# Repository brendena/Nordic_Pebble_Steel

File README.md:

# Nordic steel

The goal of this project is to replace the main motherboard in the pebble steel with newer parts.  Specifically the cpu will be a Nordic NRF52840.

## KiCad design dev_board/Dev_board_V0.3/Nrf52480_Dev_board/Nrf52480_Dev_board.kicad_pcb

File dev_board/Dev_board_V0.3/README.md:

# Changes
* Add i2c pull up resistors
* Connector cap on haptic feedback properly
* connect display signal to the adafruit display connector
* add holes and make board bigger for the watch to be attached to the board
* remove all the battery charging stuff
* on addrafruit display VDD is not connected
* add a 10 pin jtag programmer header

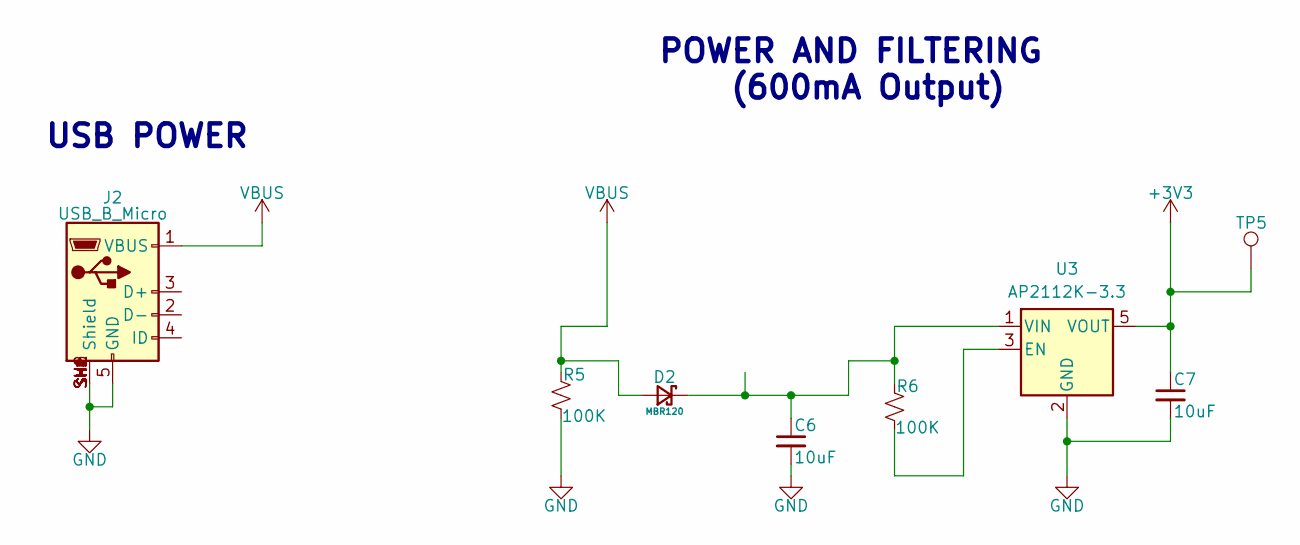
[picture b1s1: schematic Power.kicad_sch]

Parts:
C6, C7: 10uF; C_0603_1608Metric_Pad1.08x0.95mm_HandSolder
D2: MBR120; D_SOD-123F; MFR# MBR120LSFT1G
J2: USB_B_Micro; MOLEX_1050170001
R5, R6: 100K; R_0603_1608Metric_Pad0.98x0.95mm_HandSolder
TP5: TestPoint; TestPoint_Pad_1.5x1.5mm
U3: AP2112K-3.3; SOT-23-5

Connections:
+3V3: C7.1, TP5.1, U3.5 (VOUT); also elsewhere on the board
GND: C6.2, C7.2, J2.5 (GND), J2.SH1 (Shield), J2.SH2 (Shield), J2.SH3 (Shield), J2.SH4 (Shield), J2.SH5 (Shield), J2.SH6 (Shield), J2.SH7 (Shield), J2.SH8 (Shield), R5.1, U3.2 (GND); also elsewhere on the board
unnamed: C6.1, D2.1 (K), R6.2, U3.1 (VIN)
unnamed: R6.1, U3.3 (EN)
VBUS: D2.2 (A), J2.1 (VBUS), R5.2; also elsewhere on the board

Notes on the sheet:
USB POWER
POWER AND FILTERING (600mA Output)

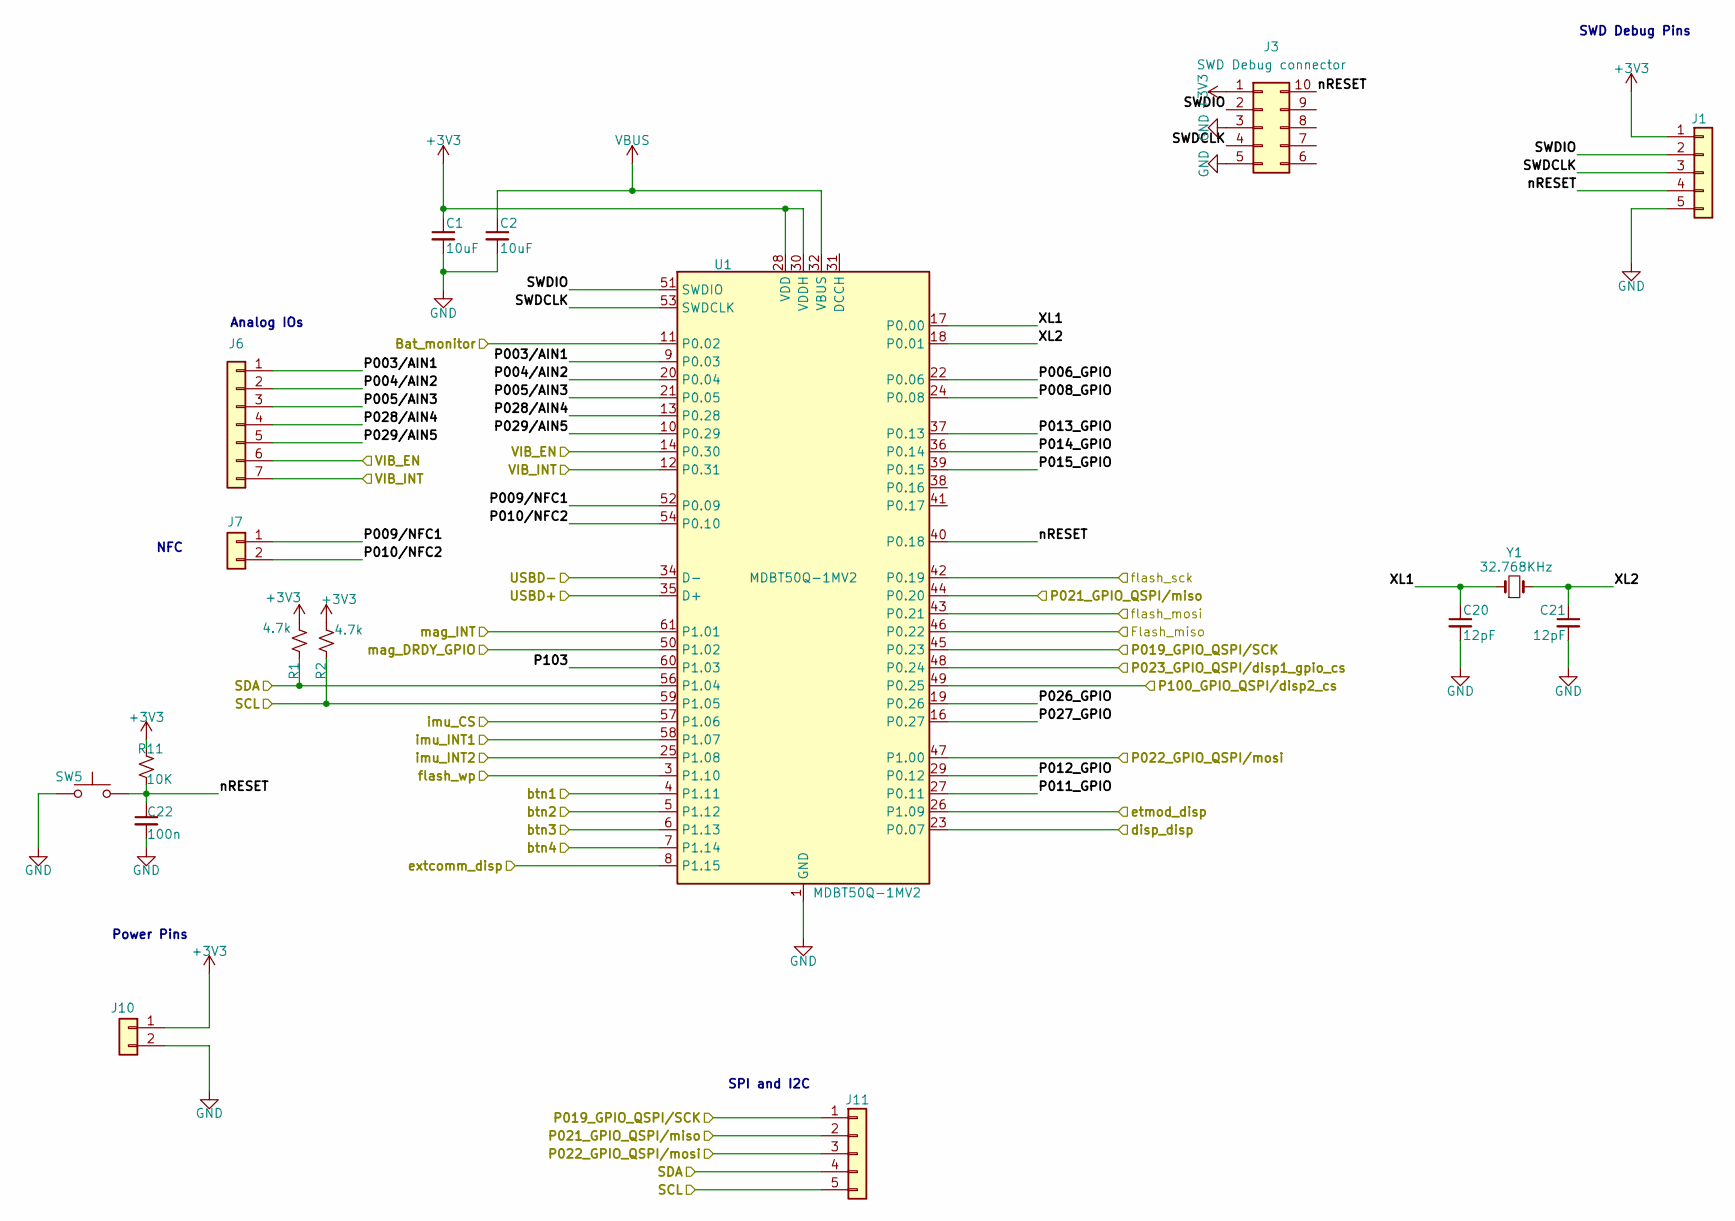
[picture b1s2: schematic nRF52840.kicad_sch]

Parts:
C1, C2: 10uF; C_0603_1608Metric_Pad1.08x0.95mm_HandSolder
C20, C21: 12pF; C_0603_1608Metric_Pad1.08x0.95mm_HandSolder
C22: 100n; C_0603_1608Metric_Pad1.08x0.95mm_HandSolder
J1, J11: Conn_01x05; PinHeader_1x05_P2.54mm_Vertical
J3: SWD Debug connector; PinHeader_2x05_P1.27mm_Vertical_SMD
J6: Conn_01x07; PinHeader_1x07_P2.54mm_Vertical
J7, J10: Conn_01x02; PinHeader_1x02_P2.54mm_Vertical
R1, R2: 4.7k; R_0603_1608Metric
R11: 10K; R_0603_1608Metric
SW5: SW_Push; SKRPACE010
U1: MDBT50Q-1MV2; Raytac_MDBT50Q; MFR# MDBT50Q-1MV2
Y1: 32.768KHz; Crystal_SMD_3215-2Pin_3.2x1.5mm

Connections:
+3V3: C1.1, J1.1, J3.1, J10.1, R1.1, R2.1, R11.2, U1.28 (VDD), U1.30 (VDDH); also elsewhere on the board
/Sensors/DISP2_CS: U1.49 (P0.25); also elsewhere on the board
/Sensors/Flash_miso: U1.46 (P0.22); also elsewhere on the board
/Sensors/SCL: J11.5, R2.2, U1.59 (P1.05); also elsewhere on the board
/Sensors/SDA: J11.4, R1.2, U1.56 (P1.04); also elsewhere on the board
/Sensors/VIB_EN: J6.6, U1.14 (P0.30); also elsewhere on the board
/Sensors/VIB_INT: J6.7, U1.12 (P0.31); also elsewhere on the board
/Sensors/btn1: U1.4 (P1.11); also elsewhere on the board
/Sensors/btn2: U1.5 (P1.12); also elsewhere on the board
/Sensors/btn3: U1.6 (P1.13); also elsewhere on the board
/Sensors/btn4: U1.7 (P1.14); also elsewhere on the board
/Sensors/disp1_GPIO_CS: U1.48 (P0.24); also elsewhere on the board
/Sensors/disp_disp: U1.23 (P0.07); also elsewhere on the board
/Sensors/etmod_disp: U1.26 (P1.09); also elsewhere on the board
/Sensors/extcomm_disp: U1.8 (P1.15); also elsewhere on the board
/Sensors/flash_mosi: U1.43 (P0.21); also elsewhere on the board
/Sensors/flash_sck: U1.42 (P0.19); also elsewhere on the board
/Sensors/flash_wp: U1.3 (P1.10); also elsewhere on the board
/Sensors/imu_CS: U1.57 (P1.06); also elsewhere on the board
/Sensors/imu_INT1: U1.58 (P1.07); also elsewhere on the board
/Sensors/imu_INT2: U1.25 (P1.08); also elsewhere on the board
/Sensors/mag_DRDY_GPIO: U1.50 (P1.02); also elsewhere on the board
/Sensors/mag_INT: U1.61 (P1.01); also elsewhere on the board
/Sensors/mosi: J11.3, U1.47 (P1.00); also elsewhere on the board
/Sensors/sck: J11.1, U1.45 (P0.23); also elsewhere on the board
/nRF52840/Bat_monitor: U1.11 (P0.02)
/nRF52840/P003/AIN1: J6.1, U1.9 (P0.03)
/nRF52840/P004/AIN2: J6.2, U1.20 (P0.04)
/nRF52840/P005/AIN3: J6.3, U1.21 (P0.05)
/nRF52840/P006_GPIO: U1.22 (P0.06)
/nRF52840/P008_GPIO: U1.24 (P0.08)
/nRF52840/P009/NFC1: J7.1, U1.52 (P0.09)
/nRF52840/P010/NFC2: J7.2, U1.54 (P0.10)
/nRF52840/P011_GPIO: U1.27 (P0.11)
/nRF52840/P012_GPIO: U1.29 (P0.12)
/nRF52840/P013_GPIO: U1.37 (P0.13)
/nRF52840/P014_GPIO: U1.36 (P0.14)
/nRF52840/P015_GPIO: U1.39 (P0.15)
/nRF52840/P021_GPIO_QSPI/miso: J11.2, U1.44 (P0.20)
/nRF52840/P026_GPIO: U1.19 (P0.26)
/nRF52840/P027_GPIO: U1.16 (P0.27)
/nRF52840/P028/AIN4: J6.4, U1.13 (P0.28)
/nRF52840/P029/AIN5: J6.5, U1.10 (P0.29)
/nRF52840/P103: U1.60 (P1.03)
/nRF52840/SWDCLK: J1.3, J3.4, U1.53 (SWDCLK)
/nRF52840/SWDIO: J1.2, J3.2, U1.51 (SWDIO)
/nRF52840/USBD+: U1.35 (D+)
/nRF52840/USBD-: U1.34 (D-)
/nRF52840/XL1: C20.1, U1.17 (P0.00), Y1.1
/nRF52840/XL2: C21.1, U1.18 (P0.01), Y1.2
/nRF52840/nRESET: C22.1, J1.4, J3.10, R11.1, SW5.2, U1.40 (P0.18)
GND: C1.2, C2.2, C20.2, C21.2, C22.2, J1.5, J3.3, J3.5, J10.2, SW5.1, U1.1 (GND), U1.2 (GND), U1.15 (GND), U1.33 (GND), U1.55 (GND); also elsewhere on the board
VBUS: C2.1, U1.32 (VBUS); also elsewhere on the board

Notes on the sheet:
Analog IOs
Power Pins
SPI and I2C
SWD Debug Pins
NFC

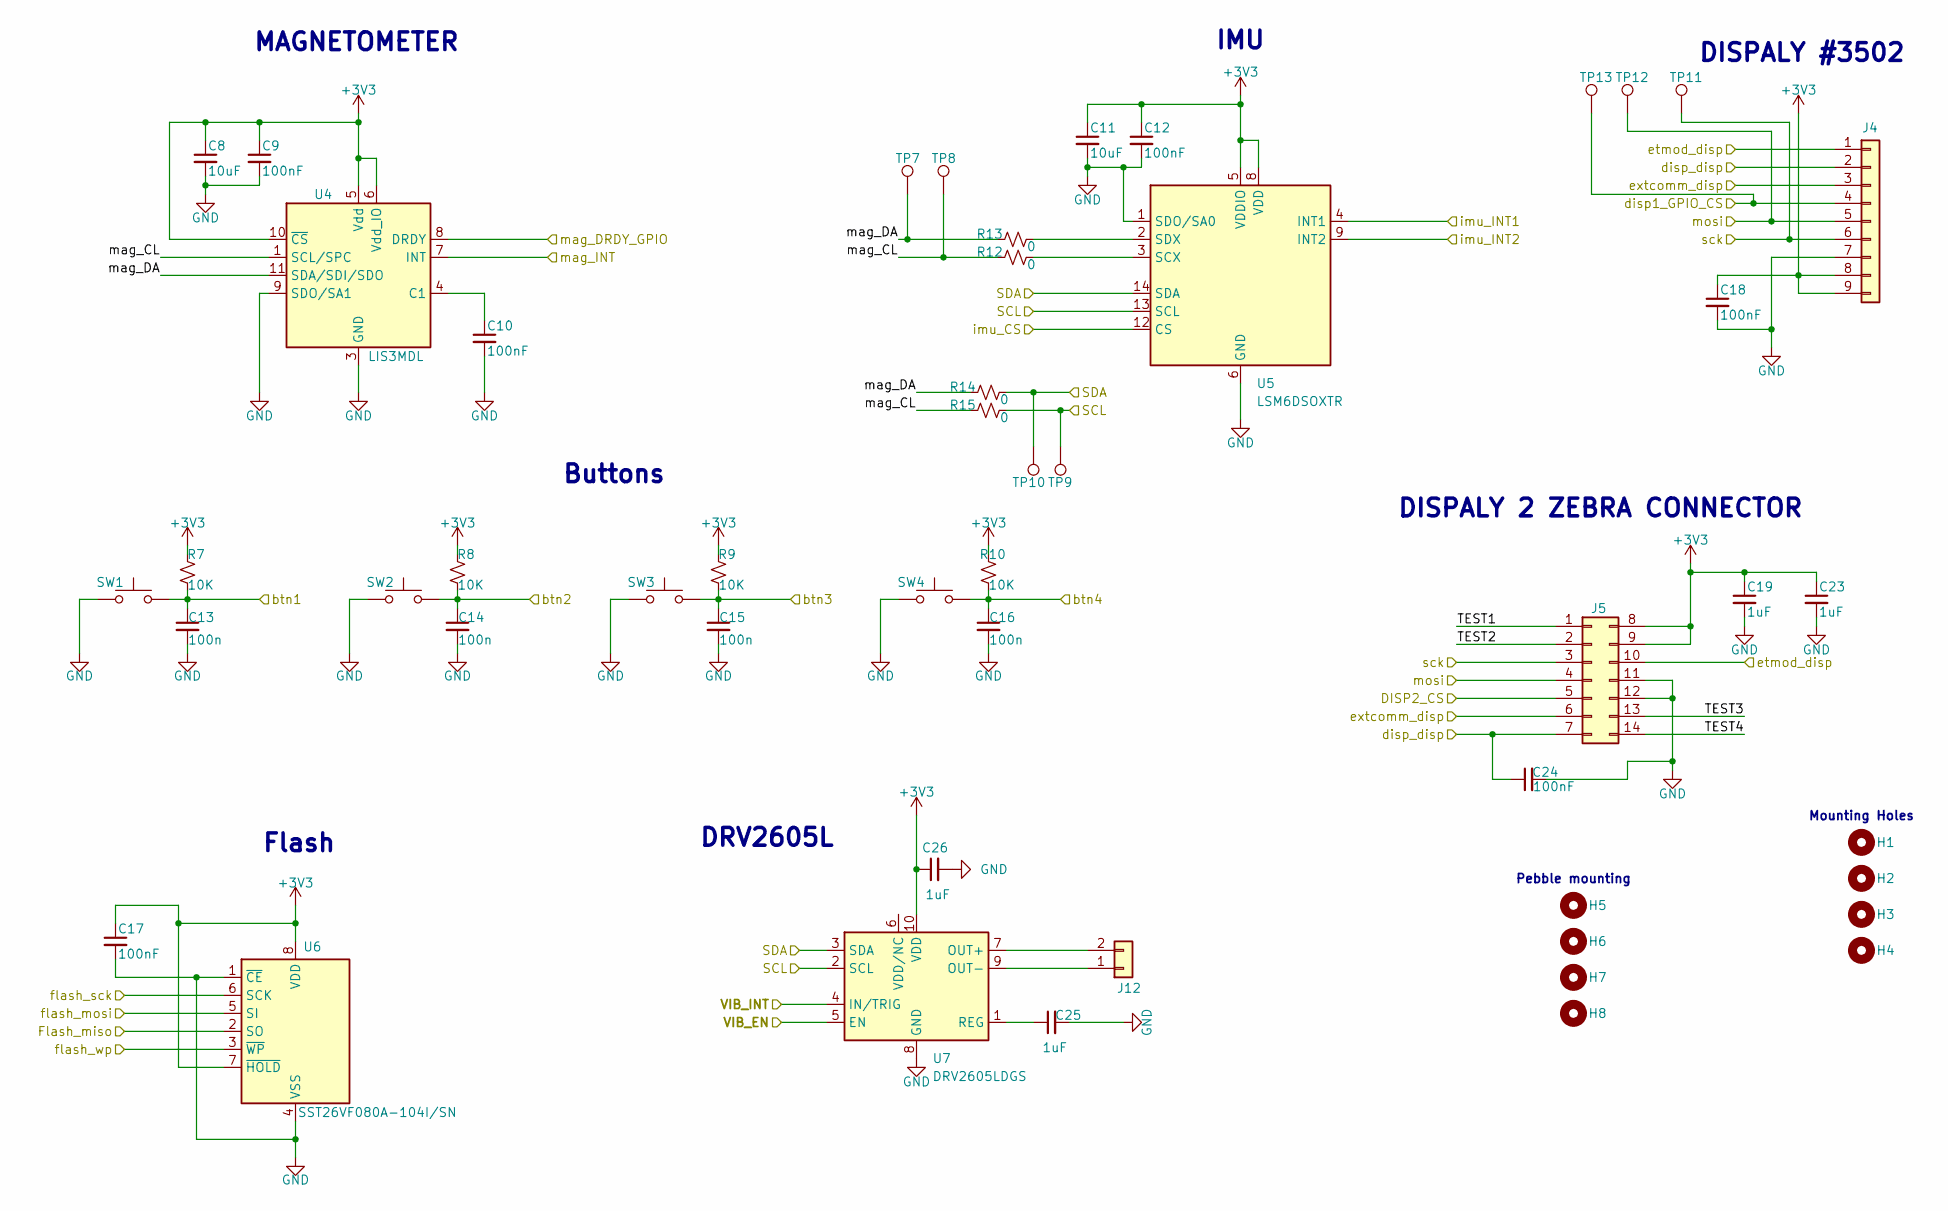
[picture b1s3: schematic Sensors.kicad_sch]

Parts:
C8, C11: 10uF; C_0603_1608Metric_Pad1.08x0.95mm_HandSolder
C9, C10, C12, C17, C18, C24: 100nF; C_0603_1608Metric_Pad1.08x0.95mm_HandSolder
C13, C14, C15, C16: 100n; C_0603_1608Metric_Pad1.08x0.95mm_HandSolder
C19, C23, C25, C26: 1uF; C_0603_1608Metric_Pad1.08x0.95mm_HandSolder
H1, H2, H3, H4: MountingHole; MountingHole_3.2mm_M3
H5, H6, H7, H8: MountingHole; MountingHole_2.1mm
J4: Conn_01x09; PinHeader_1x09_P2.54mm_Vertical
J5: Conn_02x07_Top_Bottom; Zebra_LS013B7DH01
J12: Conn_01x02; PinHeader_1x02_P2.54mm_Vertical
R7, R8, R9, R10: 10K; R_0603_1608Metric
R12, R13, R14, R15: 0; R_0603_1608Metric
SW1, SW2, SW3, SW4: SW_Push; SKRPACE010
TP7, TP8, TP9, TP10, TP11, TP12, TP13: TestPoint; TestPoint_Pad_1.5x1.5mm
U4: LIS3MDL; LGA-12_2x2mm_P0.5mm; MFR# LIS3MDLTR
U5: LSM6DSOXTR; LGA-14_3x2.5mm_P0.5mm_LayoutBorder3x4y; MFR# LSM6DSO16ISTR
U6: SST26VF080A-104I/SN; SOIC-8_3.9x4.9mm_P1.27mm; MFR# SST26VF080A-104I/SN
U7: DRV2605LDGS; VSSOP-10_3x3mm_P0.5mm

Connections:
+3V3: C8.1, C9.1, C11.1, C12.1, C17.1, C18.1, C19.1, C23.1, C26.1, J4.8, J4.9, J5.8, J5.9, R7.2, R8.2, R9.2, R10.2, U4.5 (Vdd), U4.6 (Vdd_IO), U4.10 (~CS), U5.5 (VDDIO), U5.8 (VDD), U6.7 (~HOLD), U6.8 (VDD), U7.10 (VDD); also elsewhere on the board
/Sensors/DISP2_CS: J5.5; also elsewhere on the board
/Sensors/Flash_miso: U6.2 (SO); also elsewhere on the board
/Sensors/SCL: R15.1, TP9.1, U5.13 (SCL), U7.2 (SCL); also elsewhere on the board
/Sensors/SDA: R14.1, TP10.1, U5.14 (SDA), U7.3 (SDA); also elsewhere on the board
/Sensors/TEST1: J5.1
/Sensors/TEST2: J5.2
/Sensors/TEST3: J5.13
/Sensors/TEST4: J5.14
/Sensors/VIB_EN: U7.5 (EN); also elsewhere on the board
/Sensors/VIB_INT: U7.4 (IN/TRIG); also elsewhere on the board
/Sensors/btn1: C13.1, R7.1, SW1.2; also elsewhere on the board
/Sensors/btn2: C14.1, R8.1, SW2.2; also elsewhere on the board
/Sensors/btn3: C15.1, R9.1, SW3.2; also elsewhere on the board
/Sensors/btn4: C16.1, R10.1, SW4.2; also elsewhere on the board
/Sensors/disp1_GPIO_CS: J4.4, TP13.1; also elsewhere on the board
/Sensors/disp_disp: C24.1, J4.2, J5.7; also elsewhere on the board
/Sensors/etmod_disp: J4.1, J5.10; also elsewhere on the board
/Sensors/extcomm_disp: J4.3, J5.6; also elsewhere on the board
/Sensors/flash_mosi: U6.5 (SI); also elsewhere on the board
/Sensors/flash_sck: U6.6 (SCK); also elsewhere on the board
/Sensors/flash_wp: U6.3 (~WP); also elsewhere on the board
/Sensors/imu_CS: U5.12 (CS); also elsewhere on the board
/Sensors/imu_INT1: U5.4 (INT1); also elsewhere on the board
/Sensors/imu_INT2: U5.9 (INT2); also elsewhere on the board
/Sensors/mag_CL: R12.2, R15.2, TP8.1, U4.1 (SCL/SPC)
/Sensors/mag_DA: R13.2, R14.2, TP7.1, U4.11 (SDA/SDI/SDO)
/Sensors/mag_DRDY_GPIO: U4.8 (DRDY); also elsewhere on the board
/Sensors/mag_INT: U4.7 (INT); also elsewhere on the board
/Sensors/mosi: J4.5, J5.4, TP12.1; also elsewhere on the board
/Sensors/sck: J4.6, J5.3, TP11.1; also elsewhere on the board
GND: C8.2, C9.2, C10.2, C11.2, C12.2, C13.2, C14.2, C15.2, C16.2, C17.2, C18.2, C19.2, C23.2, C24.2, C25.2, C26.2, J4.7, J5.11, J5.12, SW1.1, SW2.1, SW3.1, SW4.1, U4.2 (GND), U4.3 (GND), U4.9 (SDO/SA1), U4.12 (GND), U5.1 (SDO/SA0), U5.6 (GND), U5.7 (GND), U6.1 (~CE), U6.4 (VSS), U7.8 (GND); also elsewhere on the board
unnamed: J12.1, U7.9 (OUT-)
unnamed: J12.2, U7.7 (OUT+)
unnamed: C10.1, U4.4 (C1)
unnamed: R12.1, U5.3 (SCX)
unnamed: R13.1, U5.2 (SDX)
unnamed: C25.1, U7.1 (REG)

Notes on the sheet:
MAGNETOMETER
DISPALY #3502
Buttons
Mounting Holes
DISPALY 2 ZEBRA CONNECTOR
Pebble mounting
Flash
IMU
DRV2605L

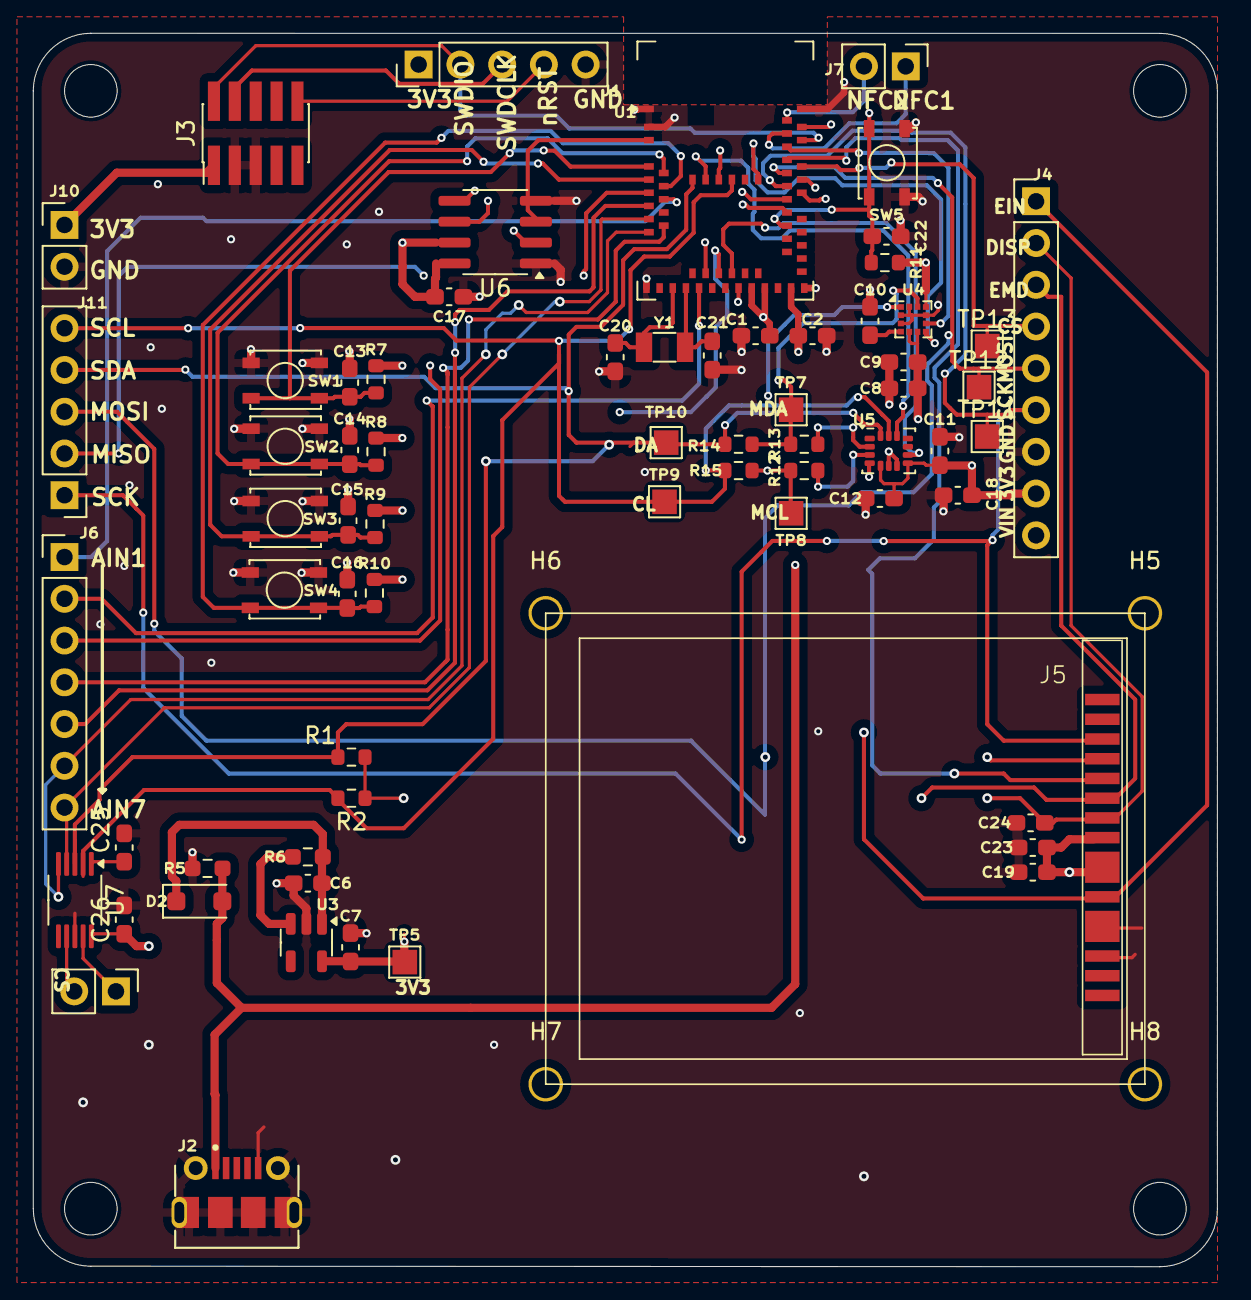
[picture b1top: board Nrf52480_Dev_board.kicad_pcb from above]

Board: 4 copper layers, 72.0 x 75.0 mm, 75 parts (0 on the bottom side), 50 nets.

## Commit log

2024-03-21 added dev board
2024-05-07 added V0.2 and removed the backups in V0.1
2024-05-17 uploaded the real dev board 0.2
2024-05-17 added the parts docs
2024-05-25 added the todo's for the next rev
2024-06-01 added v3 version almost done. Just have to adjust the holes
2024-06-01 lined the holes up
2024-06-01 lined up the holes
2024-06-11 added rev v1 of the production board
2024-06-30 pushed up V2
2024-06-30 added the power managment chip
2024-08-11 updated BOM
